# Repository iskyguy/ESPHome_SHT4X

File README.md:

# ESPHome SHT4x

KiCad hardware project for an ESPHome-oriented temperature and humidity sensor built around an ESP32-C6-WROOM-1-N8 and a Sensirion SHT40. The design includes USB-C, a BQ25628E battery charger, and an XC6220 3.3 V regulator.

Open [the project](hardware/ESPHome_SHT4X/ESPHome_SHT4X.kicad_pro) in KiCad 10. Schematic and PCB sources, review PDFs, and a 3D export are included. Some imported component libraries and models must be installed locally, and existing library paths may need adjustment.

Work in progress; no ESPHome firmware configuration is included.

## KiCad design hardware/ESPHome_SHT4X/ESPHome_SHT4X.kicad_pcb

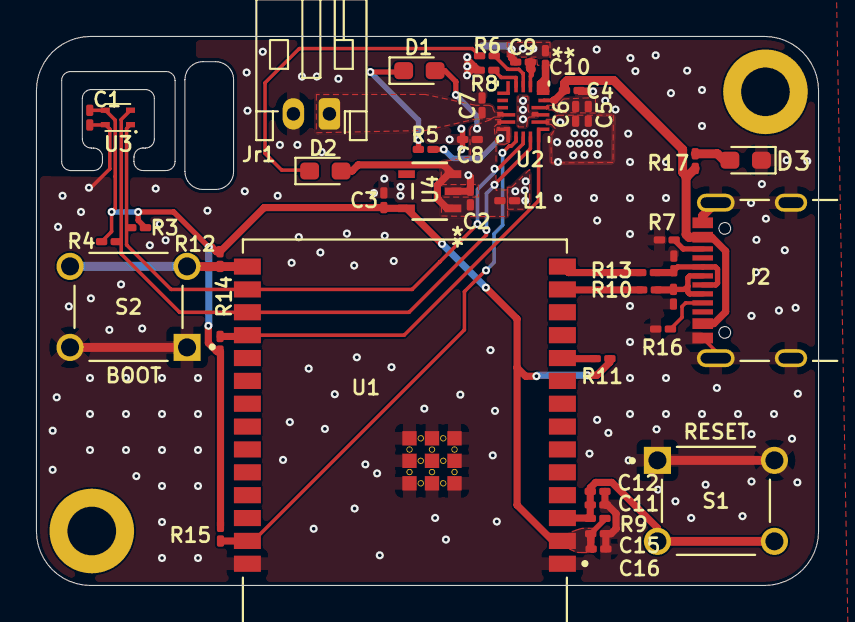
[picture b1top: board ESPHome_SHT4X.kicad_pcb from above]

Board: 2 copper layers, 43.4 x 30.5 mm, 43 parts (0 on the bottom side), 28 nets.

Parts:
C1: 100nf; C_0201_0603Metric_Pad0.64x0.40mm_HandSolder
C2, C3, C5, C7: 10uF; C_0201_0603Metric_Pad0.64x0.40mm_HandSolder
C4, C11: 1uF; C_0201_0603Metric_Pad0.64x0.40mm_HandSolder
C6, C12, C16: 0.1uF; C_0201_0603Metric_Pad0.64x0.40mm_HandSolder
C8: 20uF; C_0201_0603Metric_Pad0.64x0.40mm_HandSolder
C9: 4.6uF; C_0201_0603Metric_Pad0.64x0.40mm_HandSolder
C10: 47nF; C_0201_0603Metric_Pad0.64x0.40mm_HandSolder
C13, C14: C_Small_US; C_0201_0603Metric_Pad0.64x0.40mm_HandSolder
C15: 22uF; C_0201_0603Metric_Pad0.64x0.40mm_HandSolder
D1, D2, D3: LED; LED_0603_1608Metric_Pad1.05x0.95mm_HandSolder
J2: UJ20-C-H-G-SMT-2A-P16-TR; SAMESKY_UJ20-C-H-G-SMT-2A-P16-TR
Jr1: Conn_01x02_Pin; JST_PH_S2B-PH-K_1x02_P2.00mm_Horizontal
L1: 1uH; R_0201_0603Metric_Pad0.64x0.40mm_HandSolder
R3, R4, R9, R11, R12, R14, R15: 10k; R_0201_0603Metric_Pad0.64x0.40mm_HandSolder
R5, R6: 2.2k; R_0201_0603Metric_Pad0.64x0.40mm_HandSolder
R7, R16: 5.1k; R_0201_0603Metric_Pad0.64x0.40mm_HandSolder
R8: 2.8k; L_0201_0603Metric_Pad0.64x0.40mm_HandSolder
R10, R13: 22; L_0201_0603Metric_Pad0.64x0.40mm_HandSolder
R17: 1k; R_0201_0603Metric_Pad0.64x0.40mm_HandSolder
S1, S2: TS02-66-43-BK-100-SCR-D; SW_TS02-66-43-BK-100-SCR-D
U1: ESP32-C6-WROOM-1-N8; XCVR_ESP32-C6-WROOM-1-N8
U2: BQ25628ERYKR; WQFN-HR18__RYK_TEX
U3: SHT40-AD1F-R2; SHT4X
U4: XC6220B331MR-G; SOT-25_TOR

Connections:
*CE: R14.2, U1.18 (IO20), U2.14 (*CE)
*INT: R15.1, U1.27 (IO2), U2.11 (*INT)
BAT: C7.1, Jr1.1, U2.8 (BAT)
BTST: C10.2, U2.1 (BTST)
D+: C14.1, J2.A6 (DP1), J2.B6 (DP2), R13.2
D-: C13.1, J2.A7 (DN1), J2.B7 (DN2), R10.2
EN: C11.1, C12.1, R9.2, S1.3, S1.4, U1.3 (EN)
ESP_3V3: C1.1, C3.1, C15.1, C16.1, R3.1, R4.2, R9.1, R11.2, R12.1, R14.1, R15.2, U1.2 (3V3), U3.3 (VDD), U4.5 (VOUT)
GND: C1.2, C2.2, C3.2, C4.2, C5.2, C6.2, C7.2, C8.2, C9.2, C11.2, C12.2, C13.2, C14.2, C15.2, C16.2, D3.1 (K), J2.A1_B12 (GND), J2.B1_A12 (GND__1), J2.SH1 (SHIELD), J2.SH2 (SHIELD__1), J2.SH3 (SHIELD__2), J2.SH4 (SHIELD__3), Jr1.2, R7.2, R8.1, R16.2, S1.1, S1.2, S2.1, S2.2, U1.1 (GND), U1.28 (GND__1), U1.29_1 (GND__2), U1.29_2 (GND__3), U1.29_3 (GND__4), U1.29_4 (GND__5), U1.29_5 (GND__6), U1.29_6 (GND__7), U1.29_7 (GND__8), U1.29_8 (GND__9), U1.29_9 (GND__10), U2.15 (GND), U3.4 (VSS), U4.2 (VSS)
ILIM: R8.2, U2.4 (ILIM)
unnamed: D1.1 (K), R5.2
unnamed: D2.1 (K), R6.1
unnamed: D3.2 (A), R17.1
unnamed: J2.A5 (CC1), R16.1
unnamed: J2.B5 (CC2), R7.1
unnamed: R11.1, U1.10 (IO8)
unnamed: R12.2, S2.3, S2.4, U1.15 (IO9)
unnamed: R10.1, U1.13 (IO12)
unnamed: R13.1, U1.14 (IO13)
unnamed: R6.2, U2.3 (*PG)
unnamed: C9.1, U2.2 (REGN)
unnamed: R5.1, U2.10 (STAT)
PMID: C5.1, C6.1, U2.17 (PMID)
SCL: R4.1, U1.17 (IO19), U2.13 (SCL), U3.2 (SCL)
SDA: R3.2, U1.16 (IO18), U2.12 (SDA), U3.1 (SDA)
SW: C10.1, L1.1, U2.16 (SW)
SYS: C2.1, C8.1, D1.2 (A), D2.2 (A), L1.2, U2.9 (SYS), U4.1 (VIN), U4.3 (CE)
VBUS: C4.1, J2.A4_B9 (VBUS), J2.B4_A9 (VBUS__1), R17.2, U2.18 (VBUS)

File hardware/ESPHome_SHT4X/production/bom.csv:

Designator,Footprint,Quantity,Value,LCSC Part #
C1,0201,1,100nf,
C10,0201,1,47nF,
"C11, C4",0201,2,1uF,
"C12, C16, C6",0201,3,0.1uF,
"C13, C14",0201,2,C_Small_US,
C15,0201,1,22uF,
"C2, C3, C5, C7",0201,4,10uF,
C8,0201,1,20uF,
C9,0201,1,4.6uF,
"D1, D2, D3",0603,3,LED,
J2,SAMESKY_UJ20-C-H-G-SMT-2A-P16-TR,1,UJ20-C-H-G-SMT-2A-P16-TR,
JR1,JST_PH_S2B-PH-K_1x02_P2.00mm_Horizontal,1,Conn_01x02_Pin,
L1,0201,1,1uH,
"R10, R13",0201,2,22,
"R11, R12, R14, R15, R3, R4, R9",0201,7,10k,
"R16, R7",0201,2,5.1k,
R17,0201,1,1k,
"R5, R6",0201,2,2.2k,
R8,0201,1,2.8k,
"S1, S2",SW_TS02-66-43-BK-100-SCR-D,2,TS02-66-43-BK-100-SCR-D,
U1,XCVR_ESP32-C6-WROOM-1-N8,1,ESP32-C6-WROOM-1-N8,
U2,WQFN-HR18__RYK_TEX,1,BQ25628ERYKR,
U3,SHT4X,1,SHT40-AD1F-R2,
U4,SOT-25_TOR,1,XC6220B331MR-G,
